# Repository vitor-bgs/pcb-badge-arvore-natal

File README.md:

# Badge - Árvore de Natal

Badge feito em PCB em formato de árvore de natal.
O badge é bem simples, apenas com alguns leds para iluminar as figuras na árvore.

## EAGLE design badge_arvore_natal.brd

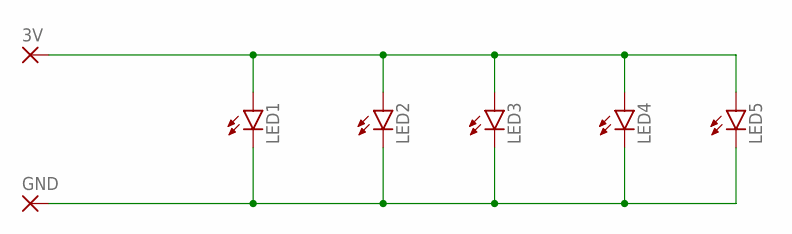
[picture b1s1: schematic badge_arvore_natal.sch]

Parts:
3V: SMD2; SMD1,27-2,54
GND: SMD2; SMD1,27-2,54
LED1, LED2, LED3, LED4, LED5: LEDCHIPLED_0805; CHIPLED_0805

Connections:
unnamed: 3V.1, LED1.A, LED2.A, LED3.A, LED4.A, LED5.A
unnamed: GND.1, LED1.C, LED2.C, LED3.C, LED4.C, LED5.C

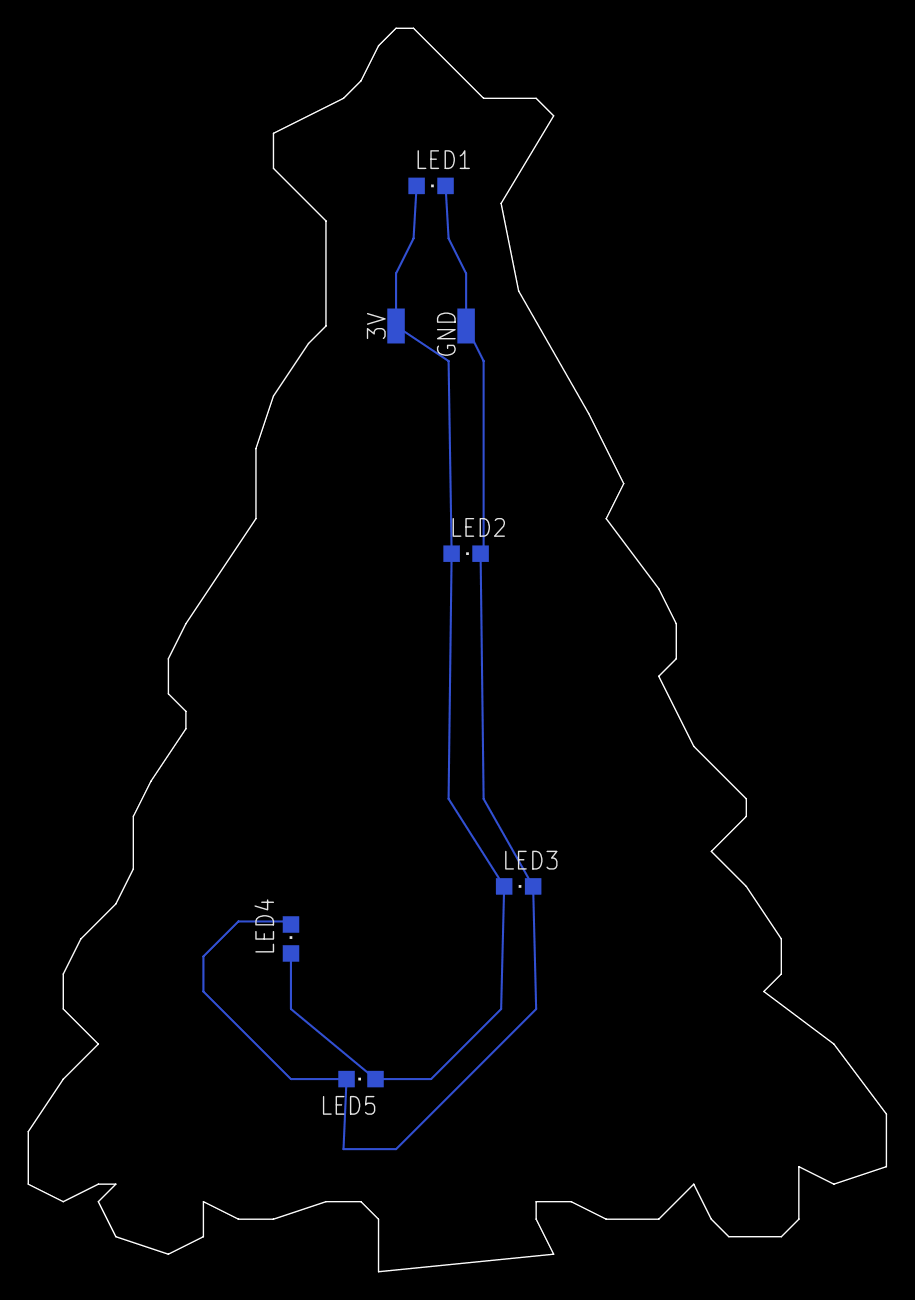
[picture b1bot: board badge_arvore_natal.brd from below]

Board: 2 copper layers, 62.2 x 90.2 mm, 7 parts (7 on the bottom side), 2 nets.

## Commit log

2020-11-23 Primeira versão do badge de arvore de natal
2020-11-23 Imagens da placa
